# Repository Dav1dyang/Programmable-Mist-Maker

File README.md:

# Programmable Mist Maker

**Open-source, programmable ultrasonic mist maker kits** — by
[shuang cai](https://shuangcai.cargo.site/) & [David Yang](https://davidyang.work/) at ByProduct Lab.

📖 **[Documentation](https://docs.byproductlab.com/)** ·
🛒 **[Buy a kit](https://shop.byproductlab.com)** ·
📜 [OSHWA certified US002742](https://certification.oshwa.org/us002742.html) ·
✍️ [Build story on Hackster](https://www.hackster.io/dav1dyang/waste-into-wonder-making-programmable-mist-makers-fe3ae7)

Most mist-maker circuits online are undocumented black boxes. This project fills that
gap: tested reference circuits, full KiCad sources, an Arduino library, and honest
notes about what went wrong along the way — so creators, educators, and engineers can
explore mist as a material. First presented as a hands-on workshop at the
**Open Hardware Summit 2025**.

## The boards

| Board | Power | Best for | Status |
|---|---|---|---|
| [**Extension Kit**](variants/xiao-extension-kit/) | USB-C | First builds, desks, classrooms | V0.1 — hardware + firmware ready |
| [**Battery Kit**](variants/battery-kit/) | Li-Po + USB-C | Portable builds, installations | **V0.4.1 — in production, bench-validated** |
| [**Block Kit**](variants/block-kit/) | Li-Po + USB-C | Drop-in container UX, 14 LEDs | V0.1 — demoed at OHS 2026 |
| [**I2C MultiPack**](variants/i2c-multipack-kit/) | TBD | Multi-emitter installations | In design |
| [**Legacy V1.4**](legacy/v1-4/) | USB / Li-Po | Reproducing the original workshop kit | Shipped, frozen |

<p align="center"><em>The two shipping boards: Extension Kit V0.1 (left) and Battery Kit V0.4.1 (right).</em></p>

Each variant folder has its own README with pin maps, an order-ready BOM + JLCPCB
production files, and build instructions. Board-by-board guides with **interactive
schematics** live on the [documentation site](https://docs.byproductlab.com/).

## Start here

1. **Pick a board** — the [Extension Kit](https://docs.byproductlab.com/boards/extension-kit/)
   is the easiest first build; the [Battery Kit](https://docs.byproductlab.com/boards/battery-kit/)
   cuts the cord. (Or [buy one assembled and tested](https://shop.byproductlab.com).)
2. **Flash the variant's BringUp sketch** to verify the hardware feature by feature.
3. **Install the [MistMaker Arduino library](https://github.com/owochel/MistMaker)** (v2.2+)
   and work through the examples: `Blink` → `Breath` → `WaterDetect` →
   `PhoneDemo` (control it from your phone).
4. **Smart home?** [`firmware-examples/home-assistant/`](firmware-examples/home-assistant/)
   joins Home Assistant with no code at all (ESPHome).

## How it works

An ESP32 drives a piezo disc at its **108.7 kHz** resonance through a MOSFET and a
3-legged tapped inductor — an autotransformer + LC tank that steps 5 V up to the
~80 Vpp the disc needs, while a current-sense amp lets the firmware detect the
disc and the water level on one ADC pin. The full story — atomization science, why
that strange inductor is everywhere in Shenzhen and nowhere at DigiKey, and a
verified alternative circuit — is at
[docs.byproductlab.com/how-it-works](https://docs.byproductlab.com/how-it-works/).

## Repo map

| Path | Contents |
|---|---|
| `variants/<board>/` | Per-board KiCad project, BOM, production files, BringUp firmware, enclosure |
| `legacy/v1-4/` | The original workshop kit, preserved as documented (incl. duck & UFO enclosure STLs) |
| `firmware-examples/` | ESPHome / Home Assistant configs |
| `docs/` | The [documentation site](https://docs.byproductlab.com/) (MkDocs), incl. `docs/assets/photos/` |
| `assets/` | Legacy V1.4 photos and the design-progress GIFs |

> [!NOTE]
> Reproducing the **legacy V1.4 board**? It has a few quirks the V0.x boards designed
> away (power sequencing, upload-while-misting) — fixes are preserved on the
> [Legacy V1.4 docs page](https://docs.byproductlab.com/boards/legacy-v1-4/).

## Use and care

> [!WARNING]
> Water + electronics + time = biology. Use distilled or clean tap water, clean the
> container regularly, and let cotton sticks dry between uses. Never run a disc
> dry for long, and never drive the circuit without a disc attached. Full notes in the
> [docs](https://docs.byproductlab.com/how-it-works/#use-and-care).

## License & credits

Open source under the **MIT License**, certified open source hardware
([OSHWA US002742](https://certification.oshwa.org/us002742.html)). Designed and
tested by [David Yang](https://davidyang.work/) and
[shuang cai](https://shuangcai.cargo.site/), inspired by community
reverse-engineering and YouTube teardowns — full reference list in the
[docs](https://docs.byproductlab.com/how-it-works/#research-references).

Parts of the documentation were drafted with AI assistance; all technical content is
validated against bench measurements and datasheets.

**Contact:** [contact@byproductlab.com](mailto:contact@byproductlab.com) ·
[@dav1dyang](https://www.instagram.com/dav1dyang/)

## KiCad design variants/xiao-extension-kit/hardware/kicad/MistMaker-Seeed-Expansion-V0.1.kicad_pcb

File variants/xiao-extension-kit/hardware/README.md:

# Extension Kit V0.1 — Hardware

| File | What |
|---|---|
| [`kicad/`](kicad/) | KiCad 10 project (schematic + PCB) |
| [`MistMaker-Seeed-Extension_V0-1_SCH.pdf`](MistMaker-Seeed-Extension_V0-1_SCH.pdf) | Schematic PDF — read this first |
| [`MistMaker-Seeed-Expansion-V0.1__Assembly.pdf`](MistMaker-Seeed-Expansion-V0.1__Assembly.pdf) | Assembly drawing |
| [`production/XiaoMistMaker_V0-1.zip`](production/) | Gerbers for JLCPCB |
| [`production/bom.csv`](production/bom.csv) | BOM with LCSC part numbers (for JLCPCB SMT assembly) |
| [`production/positions.csv`](production/positions.csv) | Pick-and-place positions |

## Ordering from JLCPCB

1. Upload `XiaoMistMaker_V0-1.zip` (defaults are fine; 1.6 mm, any color).
2. Enable **SMT assembly**, upload `bom.csv` + `positions.csv`.
3. Hand-solder afterwards: PH-2.0 piezo connector, XIAO headers.

## Key datasheets

- [INA180](https://www.ti.com/lit/ds/symlink/ina180.pdf) — current-sense amp (A3 = 100 V/V)
- [UCC27511A](https://www.ti.com/lit/ds/symlink/ucc27511a.pdf) — single-channel gate driver
- [DMT10H009LCG](https://www.diodes.com/assets/Datasheets/DMT10H009LCG.pdf) — MOSFET
- [Seeed XIAO ESP32-C6](https://wiki.seeedstudio.com/xiao_esp32c6_getting_started/)

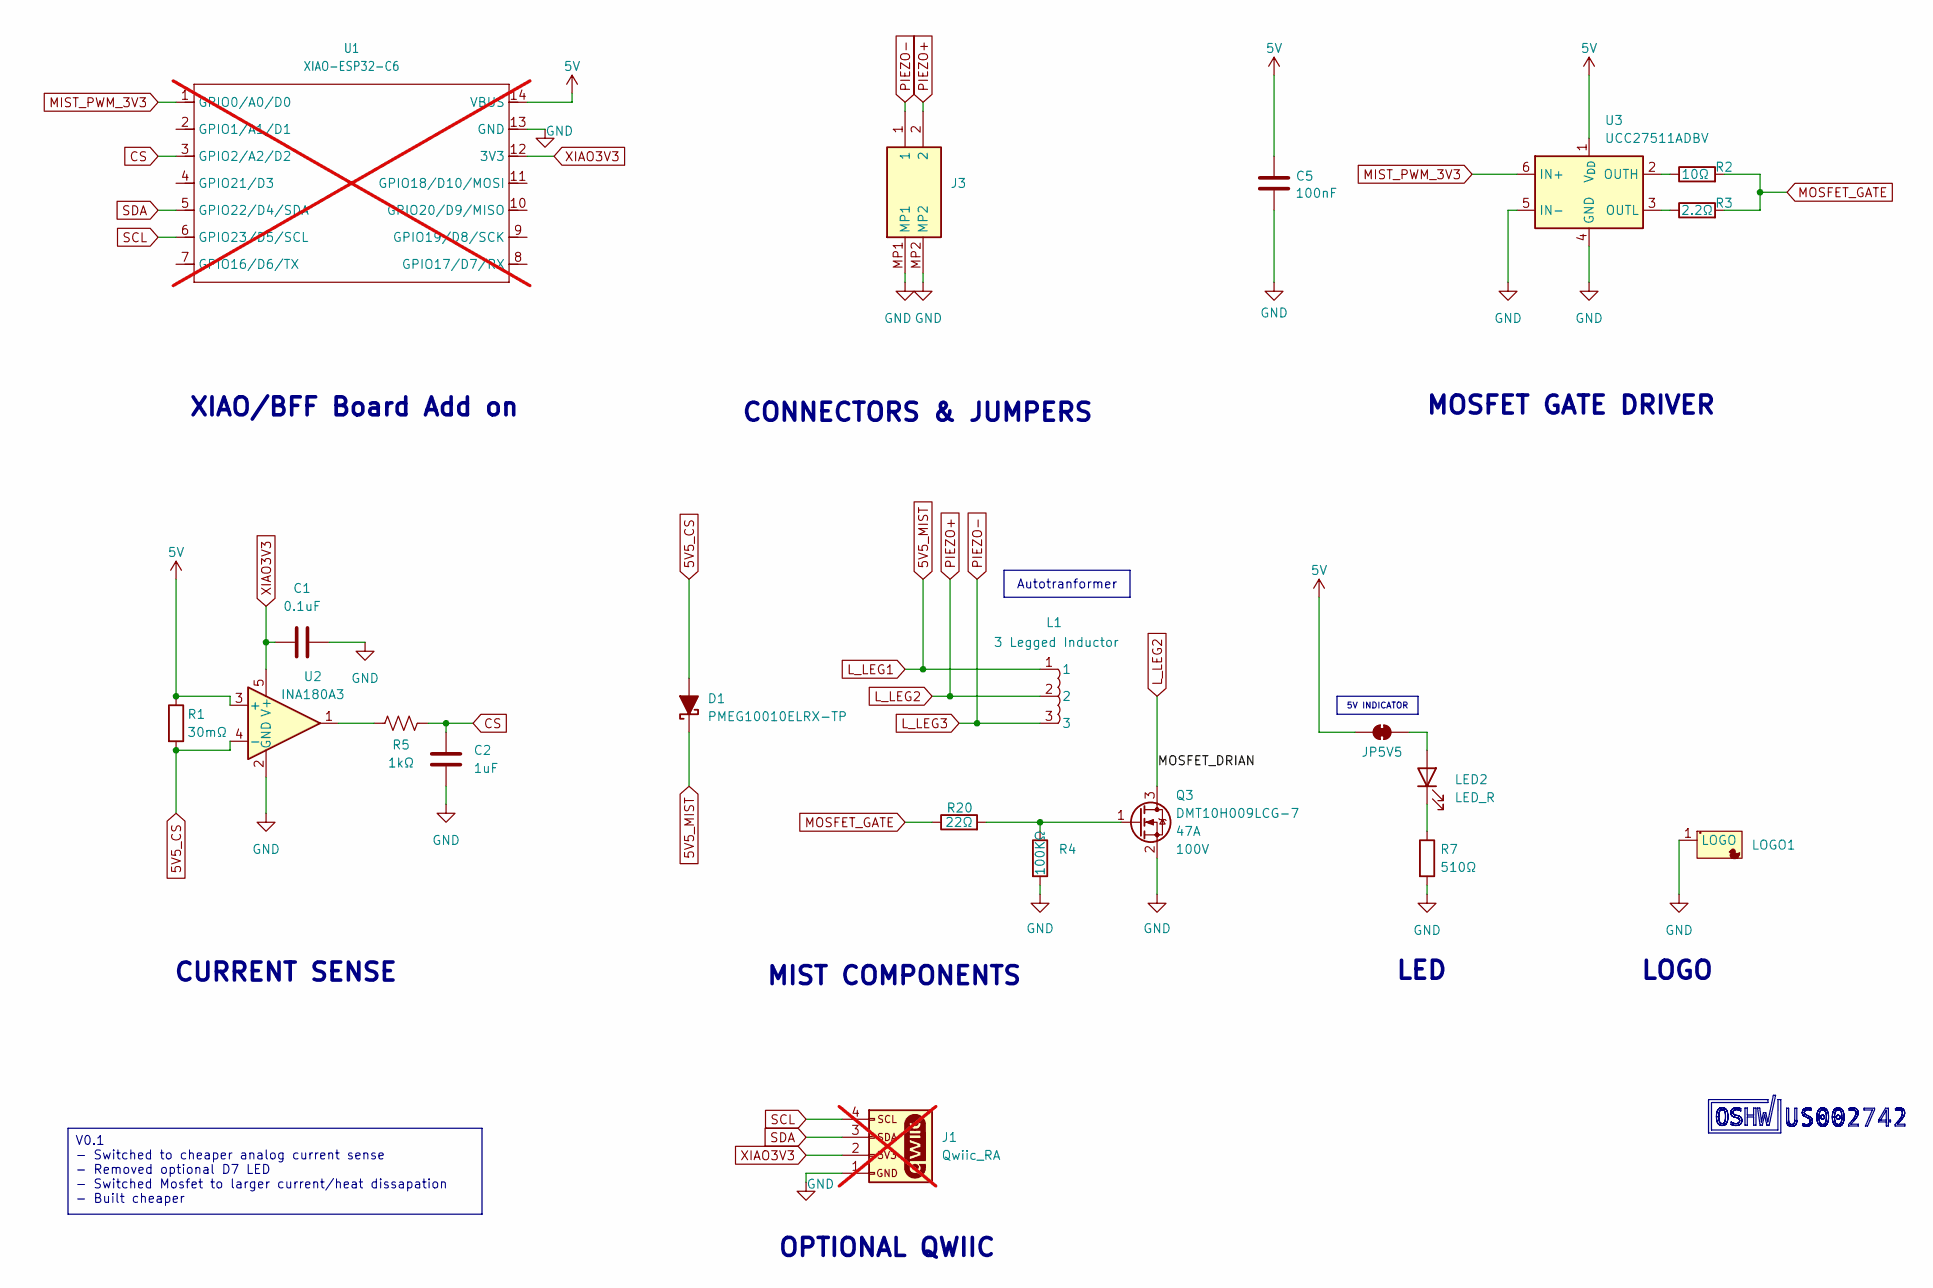
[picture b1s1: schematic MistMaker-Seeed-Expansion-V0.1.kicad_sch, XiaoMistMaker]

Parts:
C1: 0.1uF; C_0603_1608Metric; LCSC C14663
C2: 1uF; C_0402_1005Metric; LCSC C14445
C5: 100nF; C_0603; LCSC C3011705
D1: PMEG10010ELRX-TP; D_SOD-123FL; LCSC C7603319
J1: Qwiic_RA; JST_1x04_P1.0mm_Horizontal_SMD; not fitted
J3: PH-2PWB; PH2PWB; Manufacturer_Part_Number PH-2PWB; LCSC C2905019
JP5V5: SolderJumper_2_Close; SolderJumper-2_P1.3mm_Bridged_RoundedPad1.0x1.5mm
L1: 3 Legged Inductor; IND-SMD_3P-CD75; LCSC C49338546
LED2: LED_R; LED_0402_1005Metric; LCSC C25503345
LOGO1: DUCKY-LOGO
Q3: DMT10H009LCG-7; DMP3007SCG7; LCSC C461105
R1: 30mΩ; R_1206_3216Metric; LCSC C7467247
R2: 10Ω; R_0603; LCSC C22859
R3: 2.2Ω; R_0603; LCSC C22939
R4: 100KΩ; R_0603_1608Metric; JLC C14675
R5: 1kΩ; R_0402_1005Metric; LCSC C106235
R7: 510Ω; R_0402; LCSC C25123
R20: 22Ω; R_0402; LCSC C25092
U1: XIAO-ESP32-C6; XIAO-Add-On_No_Edge; not fitted
U2: INA180A3; SOT-23-5; LCSC C122882
U3: UCC27511ADBV; SOT-23-6; LCSC C2676982

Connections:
5V: C5.1, JP5V5.1 (A), R1.1, U1.14 (VBUS), U2.3 (+), U3.1 (V_{DD})
5V5_CS: D1.2 (A), R1.2, U2.4 (-)
5V5_MIST: D1.1 (K), L1.1
CS: C2.1, R5.1, U1.3 (GPIO2/A2/D2)
GND: C1.2, C2.2, C5.2, J1.1, J3.MP1, J3.MP2, LOGO1.1 (LOGO_1), Q3.2 (S), R4.2, R7.2, U1.13 (GND), U2.2 (GND), U3.4 (GND), U3.5 (IN-)
L_LEG2: J3.2, L1.2, Q3.3 (D)
L_LEG3: J3.1, L1.3
MIST_PWM_3V3: U1.1 (GPIO0/A0/D0), U3.6 (IN+)
MOSFET_GATE: R2.2, R3.2, R20.1
unnamed: JP5V5.2 (B), LED2.2 (A)
unnamed: LED2.1 (K), R7.1
unnamed: Q3.1 (G), R4.1, R20.2
unnamed: R5.2, U2.1
unnamed: R2.1, U3.2 (OUTH)
unnamed: R3.1, U3.3 (OUTL)
SCL: J1.4, U1.6 (GPIO23/D5/SCL)
SDA: J1.3, U1.5 (GPIO22/D4/SDA)
XIAO3V3: C1.1, J1.2, U1.12 (3V3), U2.5 (V+)

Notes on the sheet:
LED
XIAO/BFF Board Add on
MOSFET GATE DRIVER
CURRENT SENSE
MIST COMPONENTS
OPTIONAL QWIIC
LOGO
CONNECTORS & JUMPERS
5V INDICATOR
V0.1 - Switched to cheaper analog current sense - Removed optional D7 LED - Switched Mosfet to larger current/heat dissapation - Built cheaper
Autotranformer

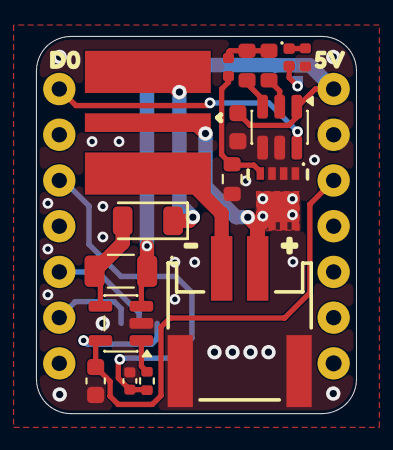
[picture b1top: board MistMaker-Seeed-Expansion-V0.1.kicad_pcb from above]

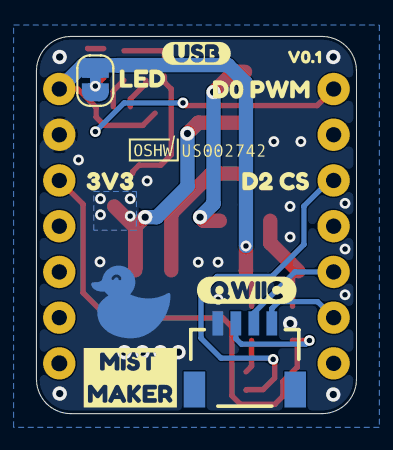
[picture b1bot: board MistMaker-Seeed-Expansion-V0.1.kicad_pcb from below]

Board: 2 copper layers, 17.8 x 21.0 mm, 33 parts (11 on the bottom side), 18 nets.

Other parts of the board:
kibuzzard-6A26391D: G***; kibuzzard-6A26391D
kibuzzard-6A263943: G***; kibuzzard-6A263943
kibuzzard-69A01650: G***; kibuzzard-69A01650
kibuzzard-69A01793: G***; kibuzzard-69A01793
kibuzzard-69DEF6AD: G***; kibuzzard-69DEF6AD
kibuzzard-69DEF161: G***; kibuzzard-69DEF161
kibuzzard-698C1293: G***; kibuzzard-698C1293
kibuzzard-698C1416: G***; kibuzzard-698C1416
kibuzzard-698C1426: G***; kibuzzard-698C1426
kibuzzard-6989FB09: G***; kibuzzard-6989FB09
kibuzzard-6989FFC2: G***; kibuzzard-6989FFC2
kibuzzard-6989FFFB: G***; kibuzzard-6989FFFB

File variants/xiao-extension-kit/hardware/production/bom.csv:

Designator,Footprint,Quantity,Value,LCSC Part #
C1,0603,1,0.1uF,C14663
C2,0402,1,1uF,C14445
C5,C_0402,1,10uF,C307415
D1,D_SOD-123FL,1,PMEG10010ELRX-TP,C7603319
J3,PH2PWB,1,PH-2PWB,C2905019
L1,IND-SMD_3P-CD75,1,3 Legged Inductor,C49338546
LED2,0402,1,LED_R,C25503345
Q3,DMP3007SCG7,1,DMT10H009LCG-7,C461105
R1,1206,1,30mΩ,C7467247
R2,R_0603,1,10Ω,C22859
R20,R_0402,1,22Ω,C25092
R3,R_0603,1,2.2Ω,C22939
R4,0603,1,100KΩ,C14675
R5,0402,1,1kΩ,C106235
R7,R_0402,1,510Ω,C25123
U2,SOT-23-5,1,INA180A3,C122882
U3,SOT-23-6,1,UCC27511ADBV,C2676982

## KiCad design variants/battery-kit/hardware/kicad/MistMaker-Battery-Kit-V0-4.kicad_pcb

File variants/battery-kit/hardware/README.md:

# Battery Kit V0.4.1 — Hardware

As-fabbed files for the **July 2026 production run** (the boards sold in the
shop). The KiCad project keeps the `V0-4` file name — the V0.4.1 changes are
edits inside it, and the production set here is the exact export that run was
built from.

| File | What |
|---|---|
| [`kicad/`](kicad/) | KiCad 10 project, **as-fabbed V0.4.1** (schematic + PCB + custom symbol/footprint libs) |
| [`MistMaker-Battery-Kit_V0-4-1_SCH.pdf`](MistMaker-Battery-Kit_V0-4-1_SCH.pdf) | Schematic PDF (plotted from the project) |
| [`production/MistMaker-Battery-Kit_0-4-1.zip`](production/) | Gerbers for JLCPCB — the ordered fileset |
| [`production/bom.csv`](production/bom.csv) | BOM with LCSC part numbers (for JLCPCB SMT assembly) |
| [`production/positions.csv`](production/positions.csv) | Pick-and-place positions |
| [`production/designators.csv`](production/designators.csv) / [`netlist.ipc`](production/netlist.ipc) | Designator map + IPC netlist from the same export |
| [`V04-Acceptance-Test_2026-07-04.md`](V04-Acceptance-Test_2026-07-04.md) | Per-board acceptance protocol (~20 min) — the automated slice runs in `BatteryKit_BringUp`'s self-test |
| [`PCB-Review_Battery-Kit-V0-4_2026-07-03_board-in-hand.md`](PCB-Review_Battery-Kit-V0-4_2026-07-03_board-in-hand.md) | Board-in-hand design review (ST sense verified, D8 margin analysis) |
| [`PCB-Review_Battery-Kit-V0-4_2026-06-22.md`](PCB-Review_Battery-Kit-V0-4_2026-06-22.md) | Pre-order design + procurement review |
| [`Duty-Cycle-Research_2026-07-03.md`](Duty-Cycle-Research_2026-07-03.md) | Measured duty→mist curve: why the 50% default, where the real maximum is (~70%) |

<!-- PHOTO: V0.4.1 assembled board, top — hardware close-up for this page -->

## Version changes

**V0.4.1** (July 2026 production run, 15 pcs — **current**):

- **R22 150 kΩ → 220 kΩ** — D8's USB-detect logic-high moves ~2.6 V → ~3.1 V,
  widening the margin over the XIAO's V<sub>IH</sub> from 0.2 V to 0.66 V (the one
  bench-marginal number population spread could have tipped across a batch).
- **R8 pull-up → pull-down (to GND)** — the ~5 V boost rail now boots **OFF**
  (LED2 dark until firmware raises D3) and deep-sleep drain drops from
  ~0.3–0.5 mA to **~0.25 mA**. Firmware-compatible: every drive path sets EN
  explicitly.
- **R7 2 kΩ → 5.1 kΩ** — LED2 dimmed to a sane brightness.
- Still deferred to V0.5: delete C14 (redundant bulk), copy the Extension's U4
  100 nF bypass placement, brighter LED3, footprint-name hygiene (IC2 carries a
  `TPS62932` footprint name; the part is a TPS2116 — electrically correct).

**V0.4** (assembled 2026-06, 5-pc prototype):

- **TPS2116 ST (mux status) routed to XIAO D8** via an R15 pull-up + R21/R22
  divider — HIGH = on USB, LOW = on the cell. The same node drives
  Q1 to disable the 3V3 LDO whenever USB is present, so the board LDO and the
  XIAO's own regulator never fight. This is the hardware fix for V0.3's
  false low-battery shutdowns on USB.
- **Charge current 500 mA → ~196 mA** (R6 = 5.1 kΩ) — keeps the SOT-23-5
  charger comfortably inside its thermal budget.

**V0.3:**

- **Battery voltage divider on D1** (`D1_BATT_VOLTAGE`, ratio 2.0) — enables the
  fuel gauge + graceful low-battery shutdown in firmware.
  (V0.3 KiCad files: see this folder's git history.)

## Ordering from JLCPCB

1. Upload `MistMaker-Battery-Kit_0-4-1.zip` (defaults fine; 1.6 mm).
2. Enable **SMT assembly**, upload `bom.csv` + `positions.csv`.
3. Hand-solder afterwards: XIAO sockets, PH-2.0 piezo + battery connectors.
4. Incoming boards: flash `BatteryKit_BringUp`, run the **automated self-test**
   (hold the button ≥ 1.5 s), then the manual steps in
   [`V04-Acceptance-Test_2026-07-04.md`](V04-Acceptance-Test_2026-07-04.md).

If you edit the schematic before ordering, re-export BOM + positions + gerbers
**as one set** (Fabrication Toolkit) — never mix a fresh zip with an old BOM.

The KiCad project uses the bundled `Mist_Custom` symbol and `Mist_Library.pretty`
footprints (paths in `sym-lib-table` / `fp-lib-table` are project-relative — it
opens standalone).

## Key datasheets

- [TPS61023](https://www.ti.com/lit/ds/symlink/tps61023.pdf) — 5.5 V boost converter
- [TPS2116](https://www.ti.com/lit/ds/symlink/tps2116.pdf) — power mux (USB/battery)
- [LP4060B5F](https://datasheet.lcsc.com/lcsc/1912111437_LOWPOWER-LP4060B5F_C517259.pdf) — Li-Po charger
- [INA180](https://www.ti.com/lit/ds/symlink/ina180.pdf) — current-sense amp (A3 = 100 V/V)
- [UCC27511A](https://www.ti.com/lit/ds/symlink/ucc27511a.pdf) — gate driver
- [DMT10H009LCG](https://www.diodes.com/assets/Datasheets/DMT10H009LCG.pdf) — MOSFET
- [Seeed XIAO ESP32-C6](https://wiki.seeedstudio.com/xiao_esp32c6_getting_started/)

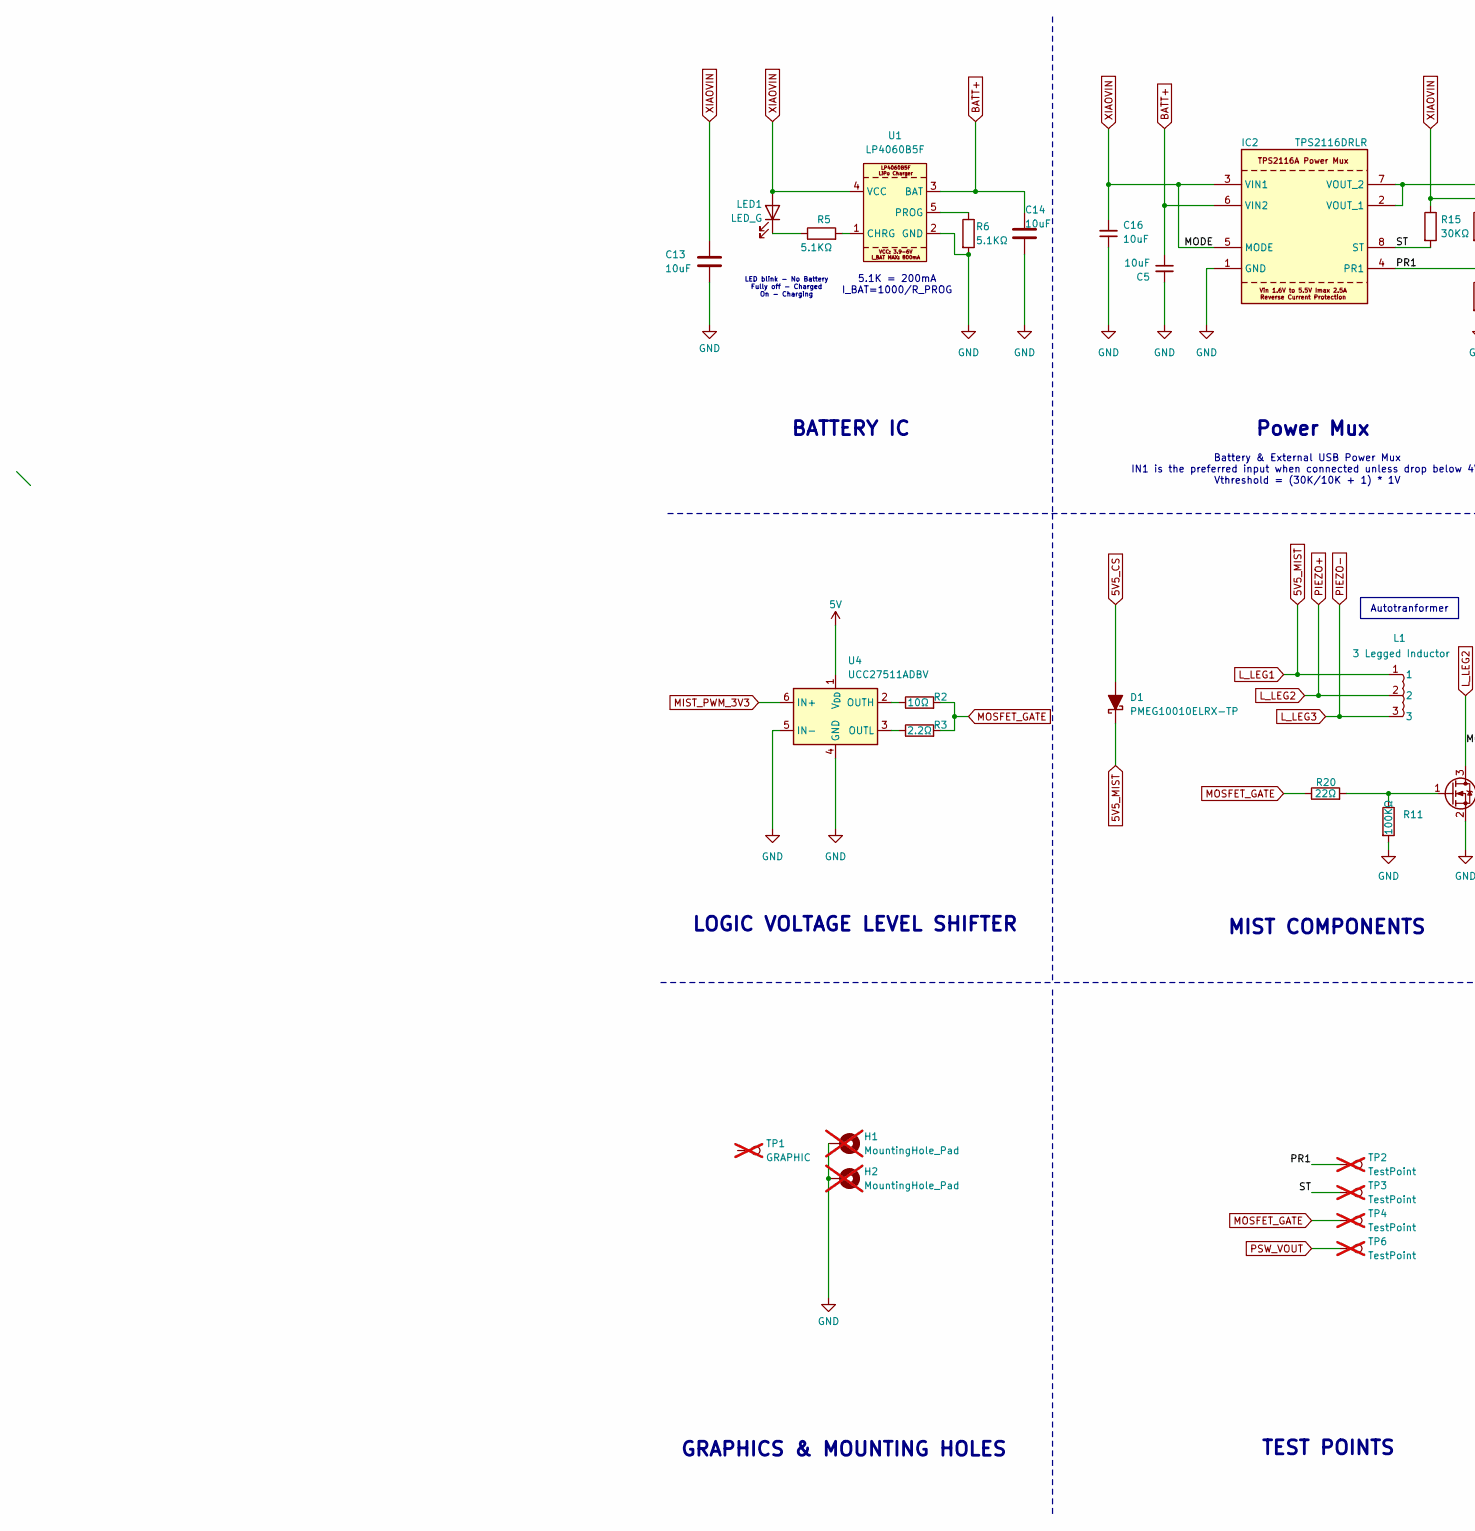
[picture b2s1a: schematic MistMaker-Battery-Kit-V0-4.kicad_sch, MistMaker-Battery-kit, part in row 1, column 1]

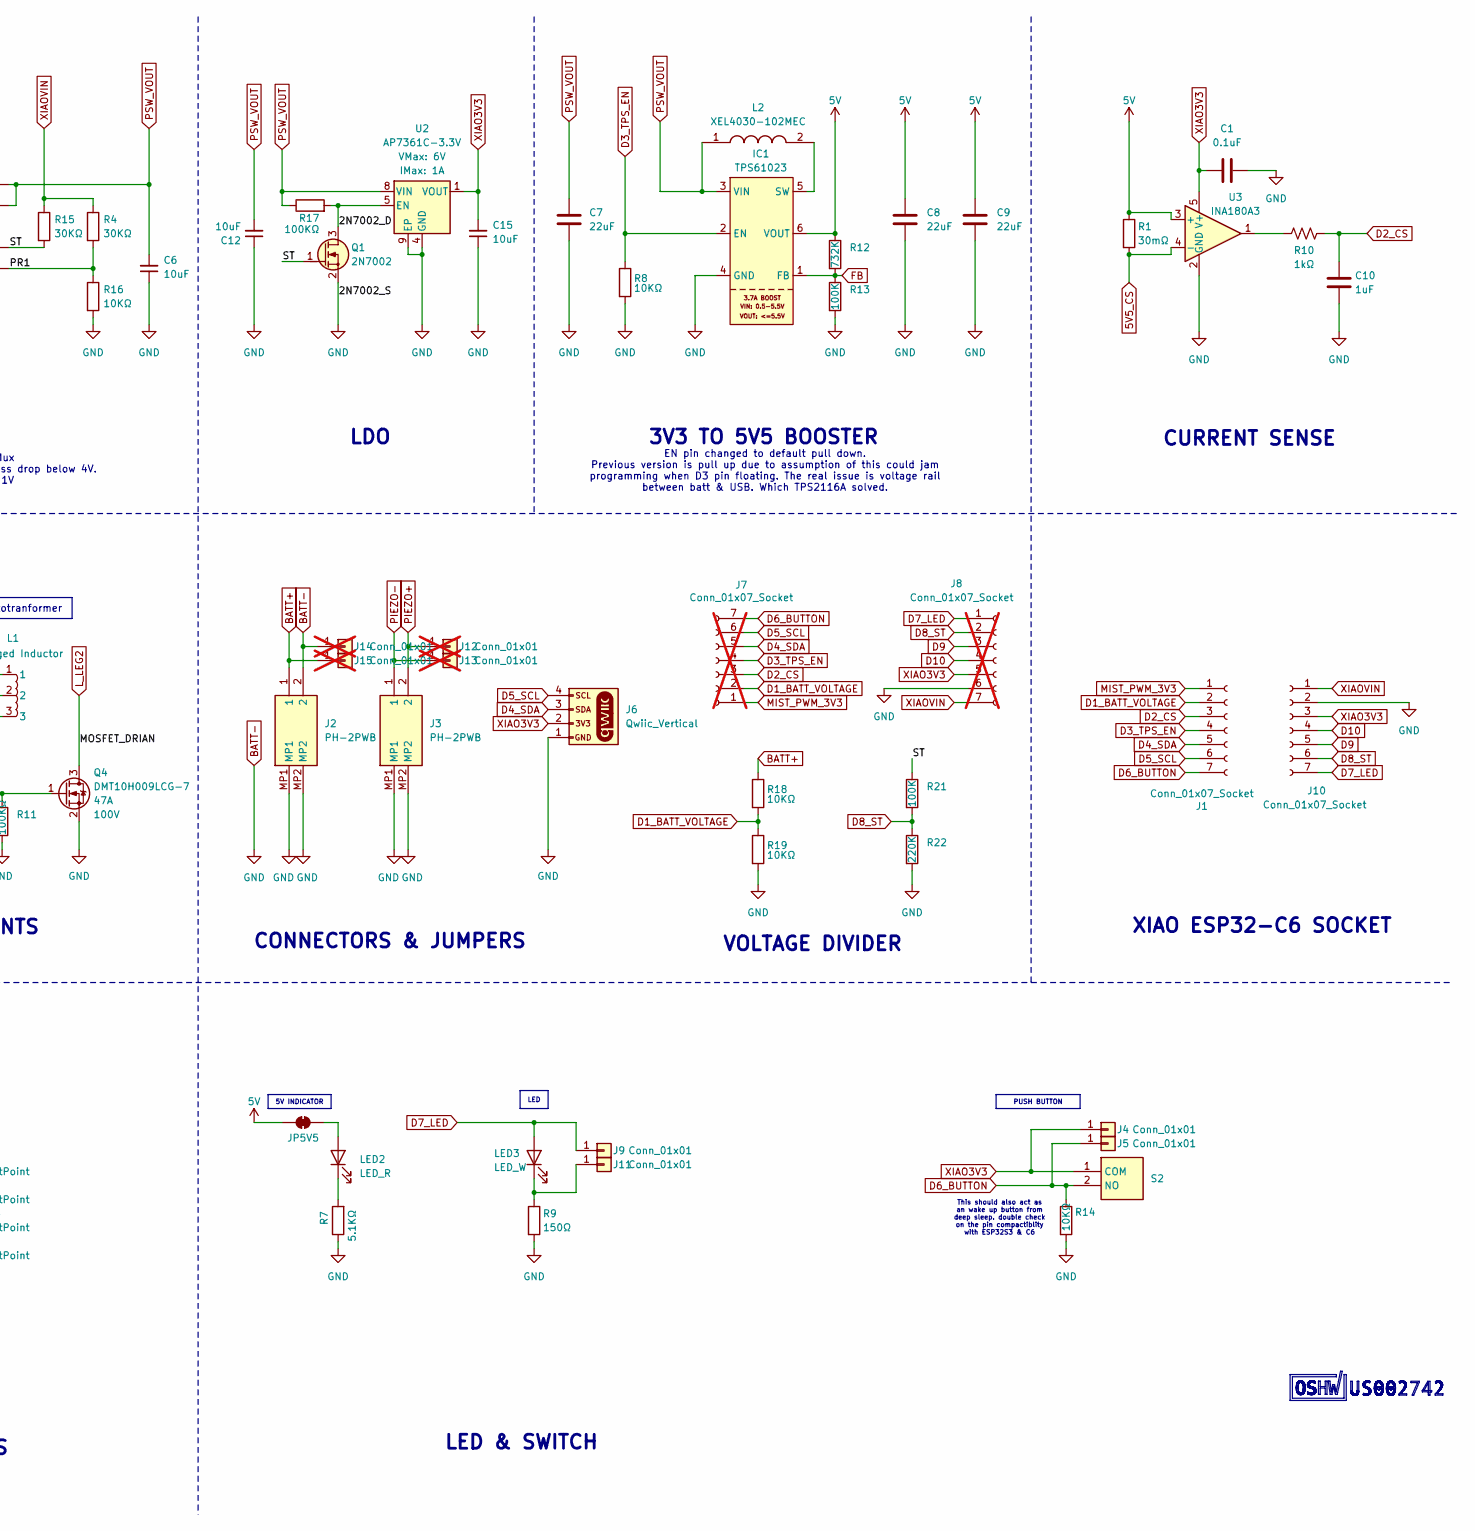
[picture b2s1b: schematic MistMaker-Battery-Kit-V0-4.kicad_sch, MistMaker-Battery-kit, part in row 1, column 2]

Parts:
C1: 0.1uF; C_0603_1608Metric; LCSC C14663
C5, C6, C12, C15, C16: 10uF; C_0603; LCSC C96446
C7, C8, C9: 22uF; C_0805_2012Metric_Pad1.18x1.45mm_HandSolder; LCSC C98190
C10: 1uF; C_0402_1005Metric; LCSC C14445
C13, C14: 10uF; C_0402; LCSC C307415
D1: PMEG10010ELRX-TP; D_SOD-123FL; LCSC C7603319
H1, H2: MountingHole_Pad; MountingHole_2.7mm_M2.5_ISO7380_Pad_SmallerPad; not fitted
IC1: TPS61023; SOT-563; LCSC C919459
IC2: TPS2116DRLR; TPS62932DRLR; Manufacturer_Part_Number TPS2116DRLR; Mouser Part Number 595-TPS2116DRLR
J1, J10: Conn_01x07_Socket; PinSocket_1x07_P2.54mm_Vertical_MiniSilk; LCSC C27985232
J2, J3: PH-2PWB; PH2PWB; Manufacturer_Part_Number PH-2PWB; LCSC C2905019
J4, J5, J9, J11: Conn_01x01; SolderWirePad_1x01_SMD_1x2mm
J6: Qwiic_Vertical; JST_1x04_P1.0mm_Vertical_SMD; LCSC C2845372
J7, J8: Conn_01x07_Socket; PinSocket_1x07_P2.54mm_Vertical; not fitted
J12, J13, J14, J15: Conn_01x01; SolderWirePad_1x01_SMD_1x2mm; not fitted
JP5V5: SolderJumper_2_Close; SolderJumper-2_P1.3mm_Bridged_RoundedPad1.0x1.5mm
L1: 3 Legged Inductor; IND-SMD_3P-CD75; LCSC C49338546
L2: XEL4030-102MEC; XEL4030102MEC; Manufacturer_Part_Number XEL4030-102MEC; Mouser Part Number 994-XEL4030-102MEC
LED1: LED_G; LED_0402_1005Metric; LCSC C965793
LED2: LED_R; LED_0402_1005Metric; LCSC C25503345
LED3: LED_W; LED_0402_1005Metric; LCSC C51933306
Q1: 2N7002; SOT-23; LCSC C8545
Q4: DMT10H009LCG-7; DMP3007SCG7; LCSC C461105
R1: 30mΩ; R_1206_3216Metric; LCSC C7467247
R2: 10Ω; R_0603; LCSC C22859
R3: 2.2Ω; R_0603; LCSC C22939
R4, R15: 30KΩ; R_0402; LCSC C138008
R5, R6, R7: 5.1KΩ; R_0402; LCSC C25905
R8, R14, R16, R18, R19: 10KΩ; R_0402; LCSC C25744
R9: 150Ω; R_0402; LCSC C25082
R10: 1kΩ; R_0402_1005Metric; LCSC C106235
R11, R17: 100KΩ; R_0603_1608Metric; LCSC C14675
R12: 732K; R_0402; LCSC C137940
R13, R21: 100K; R_0402; LCSC C25741
R20: 22Ω; R_0402; LCSC C25092
R22: 220K; R_0402; LCSC C2909335
S2: TS-1088-AR02016; TS1088AR02016; Manufacturer_Part_Number TS-1088-AR02016; LCSC C720477
TP1: GRAPHIC; DUCKY_ICON_S; not fitted
TP2, TP3, TP4, TP6: TestPoint; TestPoint-1.0mm; not fitted
U1: LP4060B5F; BATT_Charger_SOT-23-5_Min_Silk; LCSC C517259
U2: AP7361C-3.3V; DFN-8_3x3mm_P0.65mm_EP2.25x1.5mm; LCSC C151007
U3: INA180A3; SOT-23-5; LCSC C122882
U4: UCC27511ADBV; SOT-23-6; LCSC C2676982

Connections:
5V: C8.1, C9.1, IC1.6 (VOUT), JP5V5.1 (A), R1.1, R12.1, U3.3 (+), U4.1 (V_{DD})
5V5_CS: D1.2 (A), R1.2, U3.4 (-)
5V5_MIST: D1.1 (K), L1.1
/2N7002_D: Q1.3 (D), R17.2, U2.5 (EN)
/PR1: IC2.4 (PR1), R4.2, R16.1, TP2.1 (1_1)
/ST: IC2.8 (ST), Q1.1 (G), R15.2, R21.1, TP3.1 (1_1)
BATT+: C5.1, C14.2, IC2.6 (VIN2), J2.1, J15.1 (Pin_1_1), R18.1, U1.3 (BAT)
BATT-: C1.2, C5.2, C6.1, C7.2, C8.2, C9.2, C10.2, C12.1, C13.2, C14.1, C15.1, C16.1, H1.1 (1_1), H2.1 (1_1), IC1.4 (GND), IC2.1 (GND), J2.2, J2.MP1, J2.MP2, J3.MP1, J3.MP2, J6.1, J8.6, J10.2, J14.1 (Pin_1_1), Q1.2 (S), Q4.2 (S), R6.2, R7.1, R8.2, R9.2, R11.2, R13.2, R14.2, R16.2, R19.2, R22.2, U1.2 (GND), U2.4 (GND), U2.9 (EP), U3.2 (GND), U4.4 (GND), U4.5 (IN-)
D1_BATT_VOLTAGE: J1.2, J7.2, R18.2, R19.1
D2_CS: C10.1, J1.3, J7.3, R10.1
D3_TPS_EN: IC1.2 (EN), J1.4, J7.4, R8.1
D4_SDA: J1.5, J6.3, J7.5
D5_SCL: J1.6, J6.4, J7.6
D6_BUTTON: J1.7, J5.1 (Pin_1_1), J7.7, R14.1, S2.2 (NO)
D7_LED: J8.1, J9.1 (Pin_1_1), J10.7, LED3.2 (A)
D8_ST: J8.2, J10.6, R21.2, R22.1
D9: J8.3, J10.5
D10: J8.4, J10.4
FB: IC1.1 (FB), R12.2, R13.1
L_LEG2: J3.2, J12.1 (Pin_1_1), L1.2, Q4.3 (D)
L_LEG3: J3.1, J13.1 (Pin_1_1), L1.3
MIST_PWM_3V3: J1.1, J7.1, U4.6 (IN+)
MOSFET_GATE: R2.2, R3.2, R20.1, TP4.1 (1_1)
unnamed: IC1.5 (SW), L2.2
unnamed: J11.1 (Pin_1_1), LED3.1 (K), R9.1
unnamed: JP5V5.2 (B), LED2.2 (A)
unnamed: LED1.1 (K), R5.1
unnamed: LED2.1 (K), R7.2
unnamed: Q4.1 (G), R11.1, R20.2
unnamed: R10.2, U3.1
unnamed: R5.2, U1.1 (CHRG)
unnamed: R6.1, U1.5 (PROG)
unnamed: R2.1, U4.2 (OUTH)
unnamed: R3.1, U4.3 (OUTL)
PSW_VOUT: C6.2, C7.1, C12.2, IC1.3 (VIN), IC2.2 (VOUT_1), IC2.7 (VOUT_2), L2.1, R17.1, TP6.1 (1_1), U2.8 (VIN)
XIAO3V3: C1.1, C15.2, J4.1 (Pin_1_1), J6.2, J8.5, J10.3, S2.1 (COM), U2.1 (VOUT), U3.5 (V+)
XIAOVIN: C13.1, C16.2, IC2.3 (VIN1), IC2.5 (MODE), J8.7, J10.1, LED1.2 (A), R4.1, R15.1, U1.4 (VCC)

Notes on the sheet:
GRAPHICS & MOUNTING HOLES
VOLTAGE DIVIDER
CONNECTORS & JUMPERS
Battery & External USB Power Mux IN1 is the preferred input when connected unless drop below 4V. Vthreshold = (30K/10K + 1) * 1V
CURRENT SENSE
Power Mux
BATTERY IC
TEST POINTS
5.1K = 200mA I_BAT=1000/R_PROG
LDO
XIAO ESP32-C6 SOCKET
LED & SWITCH
EN pin changed to default pull down. Previous version is pull up due to assumption of this could jam programming when D3 pin floating. The real issue is voltage rail between batt & USB. Which TPS2116A solved.
LOGIC VOLTAGE LEVEL SHIFTER
3V3 TO 5V5 BOOSTER
MIST COMPONENTS
PUSH BUTTON
Autotranformer
LED blink - No Battery Fully off - Charged On - Charging
This should also act as an wake up button from deep sleep. double check on the pin compactiblity with ESP32S3 & C6
LED
5V INDICATOR

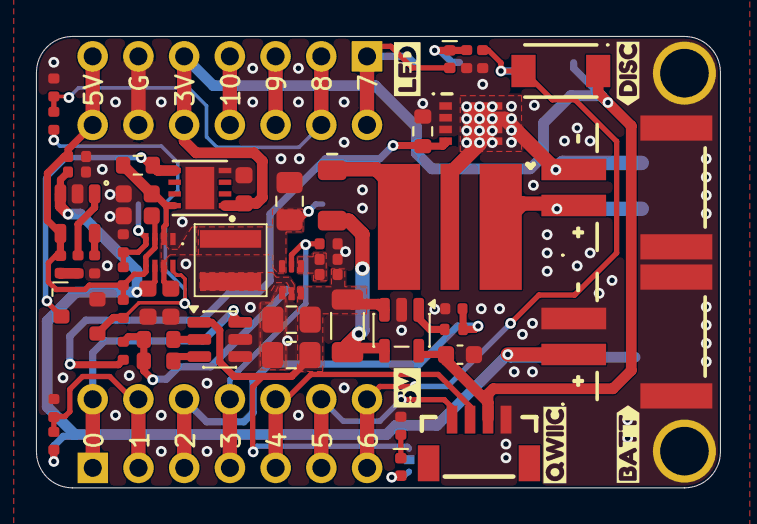
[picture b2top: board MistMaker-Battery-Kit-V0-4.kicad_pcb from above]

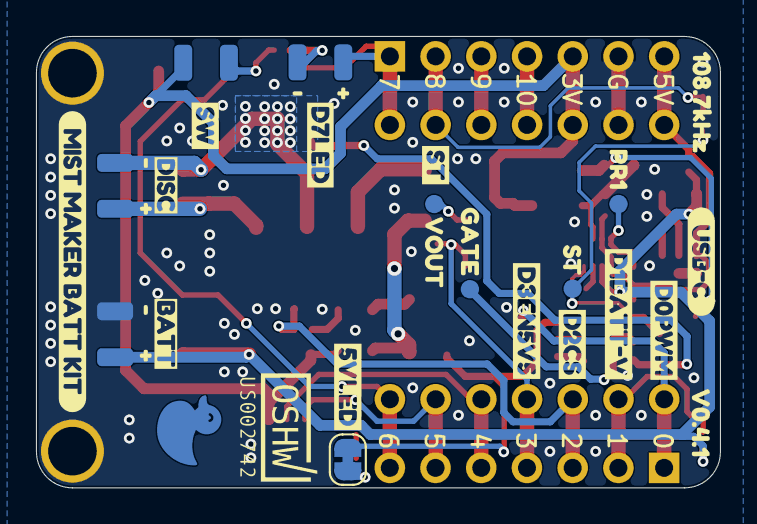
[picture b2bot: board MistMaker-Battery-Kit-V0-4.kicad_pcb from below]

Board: 2 copper layers, 38.0 x 25.1 mm, 105 parts (38 on the bottom side), 37 nets.

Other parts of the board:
kibuzzard-6A2F79F4: G***; kibuzzard-6A2F79F4
kibuzzard-6A38CD61: G***; kibuzzard-6A38CD61
kibuzzard-6A316FBE: G***; kibuzzard-6A316FBE
kibuzzard-6A317060: G***; kibuzzard-6A317060
kibuzzard-6A488614: G***; kibuzzard-6A488614
kibuzzard-69DF3D6E: G***; kibuzzard-69DF3D6E
kibuzzard-69DF3D93: G***; kibuzzard-69DF3D93
kibuzzard-69DF40D0: G***; kibuzzard-69DF40D0
kibuzzard-69DF40F6: G***; kibuzzard-69DF40F6
kibuzzard-69DF44F0, kibuzzard-69DF44F0#2: G***; kibuzzard-69DF44F0
kibuzzard-69DF407A: G***; kibuzzard-69DF407A
kibuzzard-69DF414F: G***; kibuzzard-69DF414F
kibuzzard-69DF4510, kibuzzard-69DF4510#2: G***; kibuzzard-69DF4510
kibuzzard-69E03B47: G***; kibuzzard-69E03B47
kibuzzard-69EB8B1C: G***; kibuzzard-69EB8B1C
kibuzzard-69EB8B4D: G***; kibuzzard-69EB8B4D
kibuzzard-69EB8D01: G***; kibuzzard-69EB8D01
kibuzzard-69EB47E7: G***; kibuzzard-69EB47E7
kibuzzard-69EB84CC: G***; kibuzzard-69EB84CC
kibuzzard-69EB87CA: G***; kibuzzard-69EB87CA
kibuzzard-69EB87F5: G***; kibuzzard-69EB87F5
kibuzzard-69EB470E: G***; kibuzzard-69EB470E
kibuzzard-69EB898A, kibuzzard-69EB898A#2, kibuzzard-69EB898A#3: G***; kibuzzard-69EB898A
kibuzzard-69EB4726: G***; kibuzzard-69EB4726
kibuzzard-69EB8824: G***; kibuzzard-69EB8824
kibuzzard-69EB8840: G***; kibuzzard-69EB8840
kibuzzard-69EB8976, kibuzzard-69EB8976#2, kibuzzard-69EB8976#3: G***; kibuzzard-69EB8976

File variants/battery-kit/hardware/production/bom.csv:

Designator,Footprint,Quantity,Value,LCSC Part #
C1,0603,1,0.1uF,C14663
C10,0402,1,1uF,C14445
"C12, C15, C16, C5, C6",C_0603,5,10uF,C96446
"C13, C14",C_0402,2,10uF,C307415
"C7, C8, C9",0805,3,22uF,C98190
D1,D_SOD-123FL,1,PMEG10010ELRX-TP,C7603319
IC1,SOT-563,1,TPS61023,C919459
IC2,TPS62932DRLR,1,TPS2116DRLR,C3235557
"J1, J10",PinSocket_1x07_P2.54mm_Vertical_MiniSilk,2,Conn_01x07_Socket,C27985232
"J2, J3",PH2PWB,2,PH-2PWB,C2905019
J6,JST_1x04_P1.0mm_Vertical_SMD,1,Qwiic_Vertical,C2845372
L1,IND-SMD_3P-CD75,1,3 Legged Inductor,C49338546
L2,XEL4030102MEC,1,XEL4030-102MEC,C5441341
LED1,0402,1,LED_G,C965793
LED2,0402,1,LED_R,C25503345
LED3,0402,1,LED_W,C51933306
Q1,SOT-23,1,2N7002,C8545
Q4,DMP3007SCG7,1,DMT10H009LCG-7,C461105
R1,1206,1,30mΩ,C7467247
R10,0402,1,1kΩ,C106235
"R11, R17",0603,2,100KΩ,C14675
R12,R_0402,1,732K,C137940
"R13, R21",R_0402,2,100K,C25741
"R14, R16, R18, R19, R8",R_0402,5,10KΩ,C25744
"R15, R4",R_0402,2,30KΩ,C138008
R2,R_0603,1,10Ω,C22859
R20,R_0402,1,22Ω,C25092
R22,R_0402,1,220K,C2909335
R3,R_0603,1,2.2Ω,C22939
"R5, R6, R7",R_0402,3,5.1KΩ,C25905
R9,R_0402,1,150Ω,C25082
S2,TS1088AR02016,1,TS-1088-AR02016,C720477
U1,BATT_Charger_SOT-23-5_Min_Silk,1,LP4060B5F,C517259
U2,DFN-8_3x3mm_P0.65mm_EP2.25x1.5mm,1,AP7361C-3.3V,C151007
U3,SOT-23-5,1,INA180A3,C122882
U4,SOT-23-6,1,UCC27511ADBV,C2676982
